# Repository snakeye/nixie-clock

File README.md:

# Nixie Clock

An ESP32-C3 powered Nixie clock built around custom KiCad hardware and Arduino firmware.

## Boards

### Main board

### Indicator board

## What this is

This repository contains the hardware and firmware for a four-digit Nixie clock.
It uses Wi-Fi to sync time from NTP, drives the tubes with a multiplexed display stage, and keeps the high-voltage supply disabled until the clock has a valid time.

## Features

- Wi-Fi time sync via NTP
- Automatic high-voltage safety control
- OTA firmware updates
- Manual cathode cleaning from a button long-press
- Automatic daily cathode cleaning at midnight
- KiCad hardware for the main clock board and indicator board

## Key components

- IN-14 Nixie tubes
- 155ИД1 high-voltage digit driver
- ESP32-C3 SuperMini module
- 74HC595 shift register
- TLP627 optocouplers
- Nixie Tube Boost Converter module
- WS2812B RGB status LED
- USB-C power input
- Two push buttons

### High-voltage boost module

I've used this particular module found on AliExpress. It features voltage adjustment. Other modules should also work, but they'll require proper wiring. 

## How it works

The firmware boots in a safe state with the display blanked and the high-voltage rail off.
After Wi-Fi connects and NTP provides a valid time, the clock enables the high-voltage section and starts showing the current time.

When a successful sync happens, the firmware opens a short OTA maintenance window. If an upload starts, the high-voltage rail is disabled while the update is in progress.

Button 1 has a long-press action that starts cathode cleaning manually. The same cleaning routine also runs automatically once per day when the clock reaches midnight.

## Repository layout

- `firmware/` - PlatformIO project for the ESP32-C3
- `hardware/main/` - main KiCad project for the clock board
- `hardware/indicators/` - indicator-board KiCad project
- `docs/` - photos and other documentation assets

## Firmware setup

1. Open `firmware/` in PlatformIO or your preferred VS Code setup.
2. Copy `firmware/src/config.h.example` to `firmware/src/config.h`.
3. Fill in your Wi-Fi SSID and password.
4. Build and upload the `esp32c3` environment.

The firmware is configured for the `esp32-c3-devkitm-1` board.

## Notes

- The clock currently uses a CET/CEST timezone definition in firmware.
- The firmware hostname is `nixie-clock`.
- `firmware/src/config.h` is ignored by Git so local Wi-Fi credentials stay machine-specific.

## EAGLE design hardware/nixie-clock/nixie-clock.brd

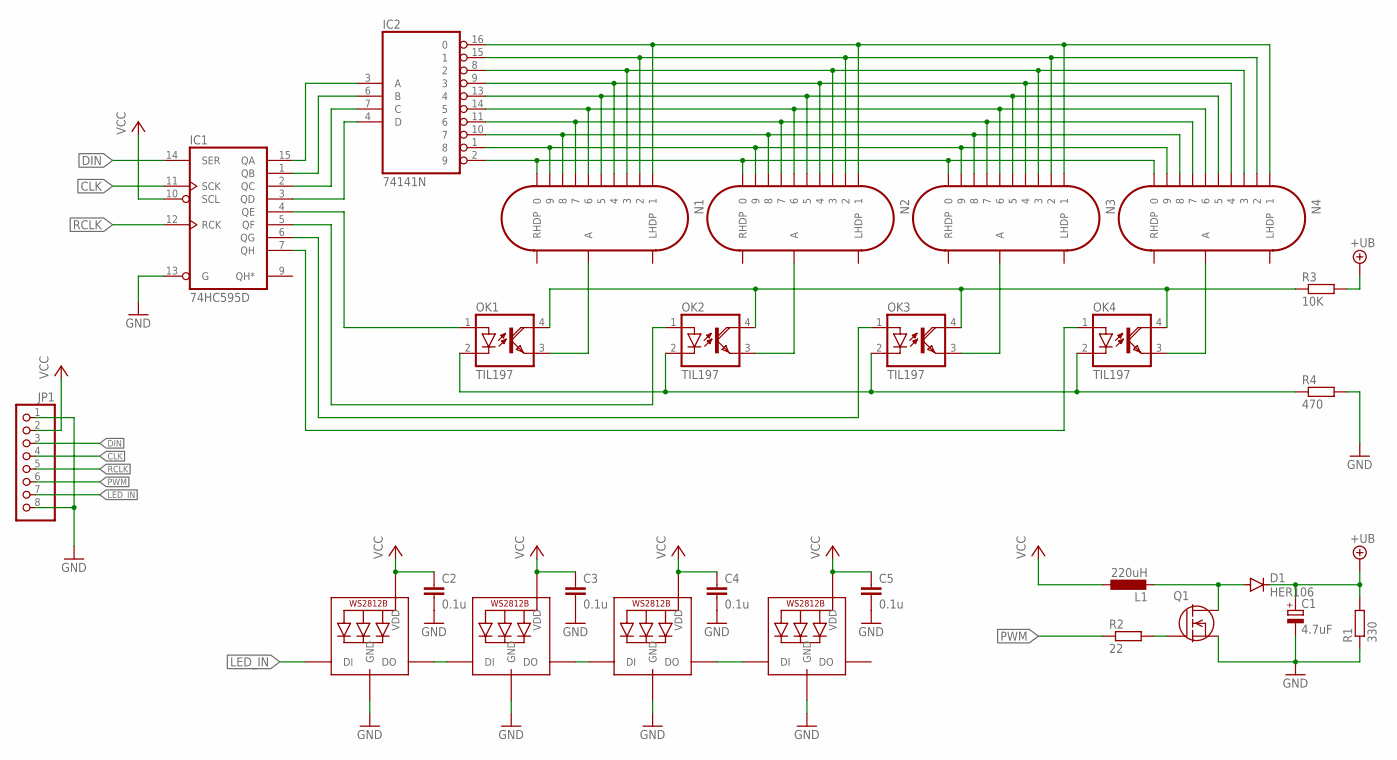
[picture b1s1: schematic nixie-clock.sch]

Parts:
C1: 4.7uF; E3,5-8
C2, C3, C4, C5: 0.1u; C0805
D1: HER106; DO15-12
IC1: 74HC595D; SO16
IC2: 74141N; DIL16
JP1: PINHD-1X8; 1X08
L1: 220uH; 6000-XXXX-RC
LED1, LED2, LED3, LED4: WS2812B_5050N; WS2812B-NARROW
N1, N2, N3, N4: IN-14
OK1, OK2, OK3, OK4: TIL197; DIL04
Q1: IRF840; TO220
R1: 330; 0207/7
R2: 22; 0207/7
R3: 10K; 0207/7
R4: 470; 0207/7

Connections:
+UB: C1.+, D1.C, R1.2, R3.2
CLK: IC1.11 (SCK), JP1.4
DIN: IC1.14 (SER), JP1.3
GND: C1.-, C2.2, C3.2, C4.2, C5.2, IC1.8 (GND), IC1.13 (G), IC2.12 (GND), JP1.1, JP1.8, LED1.3-GND (GND), LED2.3-GND (GND), LED3.3-GND (GND), LED4.3-GND (GND), Q1.3 (S), R1.1, R4.2
LED_IN: JP1.7, LED1.4-DIN (DI)
N1_ANODE: N1.A, OK1.3 (EMI)
N2_ANODE: N2.A, OK2.3 (EMI)
N3_ANODE: N3.A, OK3.3 (EMI)
N4_ANODE: N4.A, OK4.3 (EMI)
unnamed: Q1.1 (G), R2.2
unnamed: D1.A, L1.2, Q1.2 (D)
unnamed: IC2.16 (0), N1.1, N2.1, N3.1, N4.1
unnamed: IC2.15 (1), N1.2, N2.2, N3.2, N4.2
unnamed: IC2.8 (2), N1.3, N2.3, N3.3, N4.3
unnamed: IC2.9 (3), N1.4, N2.4, N3.4, N4.4
unnamed: IC2.13 (4), N1.5, N2.5, N3.5, N4.5
unnamed: IC2.14 (5), N1.6, N2.6, N3.6, N4.6
unnamed: IC2.11 (6), N1.7, N2.7, N3.7, N4.7
unnamed: IC2.10 (7), N1.8, N2.8, N3.8, N4.8
unnamed: IC2.1 (8), N1.9, N2.9, N3.9, N4.9
unnamed: IC2.2 (9), N1.0, N2.0, N3.0, N4.0
unnamed: OK1.4 (COL), OK2.4 (COL), OK3.4 (COL), OK4.4 (COL), R3.1
unnamed: OK1.2 (C), OK2.2 (C), OK3.2 (C), OK4.2 (C), R4.1
unnamed: IC1.4 (QE), OK1.1 (A)
unnamed: LED1.2-DOUT (DO), LED2.4-DIN (DI)
unnamed: IC1.6 (QG), OK3.1 (A)
unnamed: IC1.7 (QH), OK4.1 (A)
unnamed: IC1.15 (QA), IC2.3 (A)
unnamed: IC1.1 (QB), IC2.6 (B)
unnamed: IC1.2 (QC), IC2.7 (C)
unnamed: IC1.3 (QD), IC2.4 (D)
unnamed: IC1.5 (QF), OK2.1 (A)
unnamed: LED2.2-DOUT (DO), LED3.4-DIN (DI)
unnamed: LED3.2-DOUT (DO), LED4.4-DIN (DI)
PWM: JP1.6, R2.1
RCLK: IC1.12 (RCK), JP1.5
VCC: C2.1, C3.1, C4.1, C5.1, IC1.10 (SCL), IC1.16 (VCC), IC2.5 (VCC), JP1.2, L1.1, LED1.1-VDD (VDD), LED2.1-VDD (VDD), LED3.1-VDD (VDD), LED4.1-VDD (VDD)

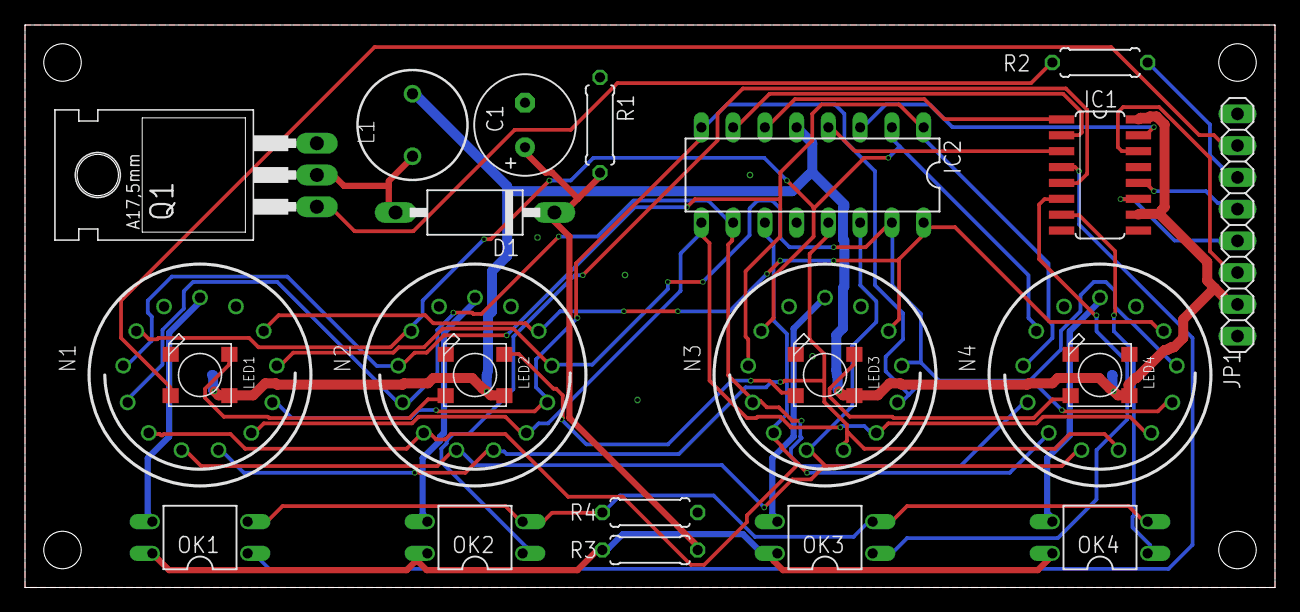
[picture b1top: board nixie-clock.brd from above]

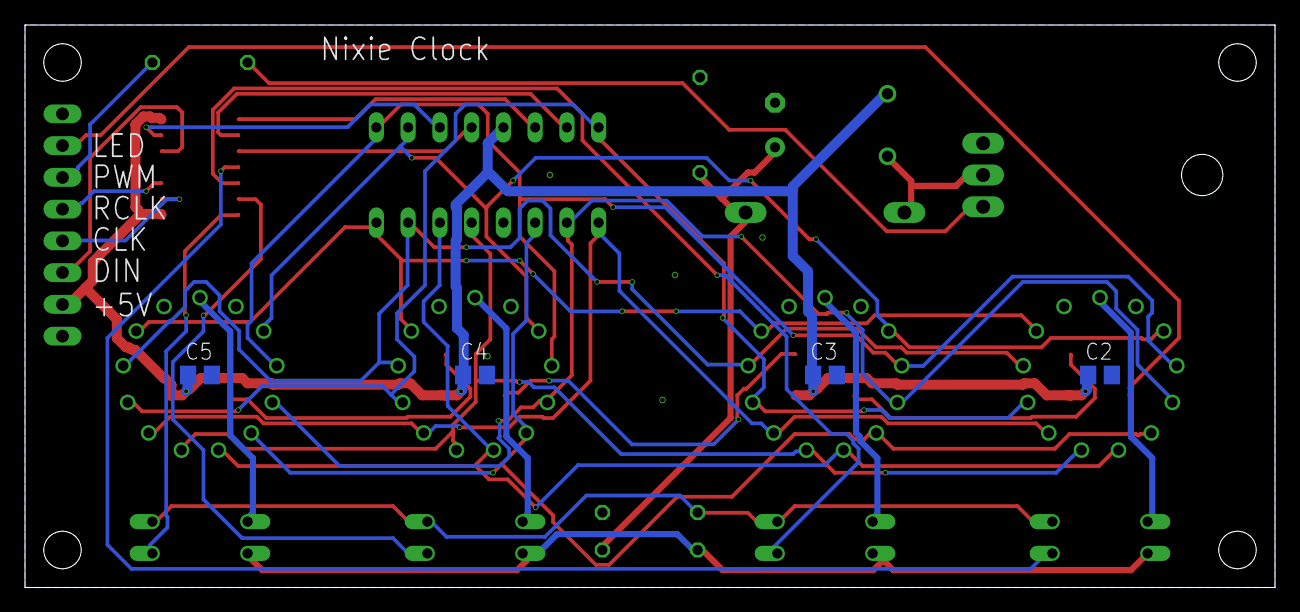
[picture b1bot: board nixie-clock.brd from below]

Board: 2 copper layers, 100.0 x 45.0 mm, 27 parts (4 on the bottom side), 37 nets.

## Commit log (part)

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2020-03-29 Board design
